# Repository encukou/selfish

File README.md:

# Selfish keyboard

This is an experiment.

Selfish layout for Moonlander is [here](https://configure.zsa.io/moonlander/layouts/DapMK/latest/0),
or, with some tweaks the configurator can't do, in [my QMK fork](https://github.com/encukou/qmk_firmware/blob/selfish/keyboards/moonlander/keymaps/selfish/keymap.c).

## Thanks

Thank you to Peter Lyons for sharing
[Squeezebox](https://peterlyons.com/problog/2022/01/squeezebox-keyboard-v2112/)!

## Legal stuff

Any file in this repository may be used either under the MIT licence or the
CC-BY-SA-40 licence, at your choice.
Please link to https://github.com/encukou/selfish for attribution.

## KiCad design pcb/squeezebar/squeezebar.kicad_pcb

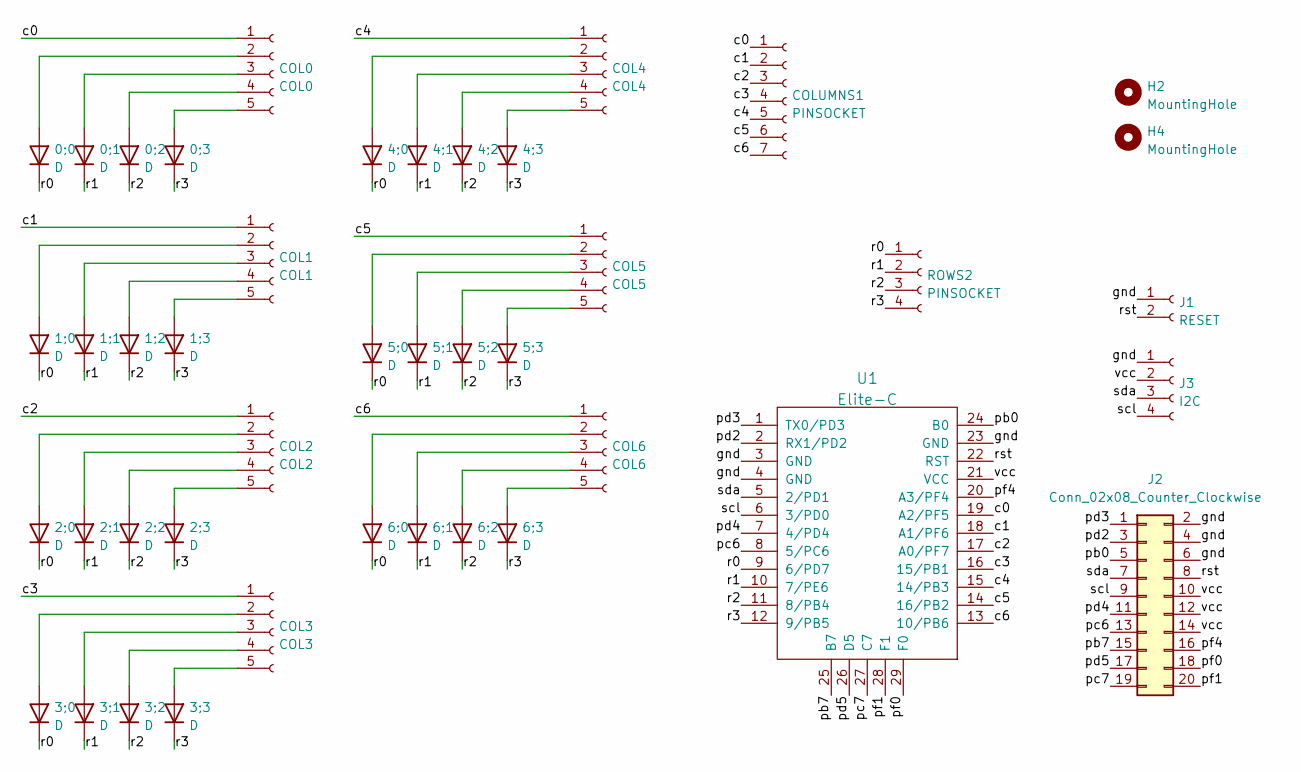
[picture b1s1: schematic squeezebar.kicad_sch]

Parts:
0;0, 0;1, 0;2, 0;3, 1;0, 1;1, 1;2, 1;3, 2;0, 2;1, 2;2, 2;3, 3;0, 3;1, 3;2, 3;3, 4;0, 4;1, 4;2, 4;3, 5;0, 5;1, 5;2, 5;3, 6;0, 6;1, 6;2, 6;3: D; Diode
COL0: COL0; PinHeader_Col_1x05_P2.54mm_Vertical
COL1: COL1; PinHeader_Col_1x05_P2.54mm_Vertical
COL2: COL2; PinHeader_Col_1x05_P2.54mm_Vertical
COL3: COL3; PinHeader_Col_1x05_P2.54mm_Vertical
COL4: COL4; PinHeader_Col_1x05_P2.54mm_Vertical
COL5: COL5; PinHeader_Col_1x05_P2.54mm_Vertical
COL6: COL6; PinHeader_Col_1x05_P2.54mm_Vertical
COLUMNS1: PINSOCKET; PinHeader_COLS_1x07_P2.54mm_Vertical
H2, H4: MountingHole; MountingHole_3.2mm_M3_DIN965
J1: RESET; PinHeader_RST_1x02_P2.54mm_Vertical
J2: Conn_02x08_Counter_Clockwise; PinSocket_2x10_P2.54mm_Vertical
J3: I2C; PinHeader_I2C_1x04_P2.54mm_Vertical
ROWS2: PINSOCKET; PinSocket_1x04_P2.54mm_Vertical_LongPads
U1: Elite-C

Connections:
/c0: COL0.1, COLUMNS1.1, U1.19 (A2/PF5)
/c1: COL1.1, COLUMNS1.2, U1.18 (A1/PF6)
/c2: COL2.1, COLUMNS1.3, U1.17 (A0/PF7)
/c3: COL3.1, COLUMNS1.4, U1.16 (15/PB1)
/c4: COL4.1, COLUMNS1.5, U1.15 (14/PB3)
/c5: COL5.1, COLUMNS1.6, U1.14 (16/PB2)
/c6: COL6.1, COLUMNS1.7, U1.13 (10/PB6)
/gnd: J1.1, J2.2, J2.4, J2.6, J3.1, U1.3 (GND), U1.4 (GND), U1.23 (GND)
/pb0: J2.5, U1.24 (B0)
/pb7: J2.15, U1.25 (B7)
/pc6: J2.13, U1.8 (5/PC6)
/pc7: J2.19, U1.27 (C7)
/pd2: J2.3, U1.2 (RX1/PD2)
/pd3: J2.1, U1.1 (TX0/PD3)
/pd4: J2.11, U1.7 (4/PD4)
/pd5: J2.17, U1.26 (D5)
/pf0: J2.18, U1.29 (F0)
/pf1: J2.20, U1.28 (F1)
/pf4: J2.16, U1.20 (A3/PF4)
/r0: 0;0.1 (K), 1;0.1 (K), 2;0.1 (K), 3;0.1 (K), 4;0.1 (K), 5;0.1 (K), 6;0.1 (K), ROWS2.1, U1.9 (6/PD7)
/r1: 0;1.1 (K), 1;1.1 (K), 2;1.1 (K), 3;1.1 (K), 4;1.1 (K), 5;1.1 (K), 6;1.1 (K), ROWS2.2, U1.10 (7/PE6)
/r2: 0;2.1 (K), 1;2.1 (K), 2;2.1 (K), 3;2.1 (K), 4;2.1 (K), 5;2.1 (K), 6;2.1 (K), ROWS2.3, U1.11 (8/PB4)
/r3: 0;3.1 (K), 1;3.1 (K), 2;3.1 (K), 3;3.1 (K), 4;3.1 (K), 5;3.1 (K), 6;3.1 (K), ROWS2.4, U1.12 (9/PB5)
/rst: J1.2, J2.8, U1.22 (RST)
/scl: J2.9, J3.4, U1.6 (3/PD0)
/sda: J2.7, J3.3, U1.5 (2/PD1)
/vcc: J2.10, J2.12, J2.14, J3.2, U1.21 (VCC)
unnamed: 0;0.2 (A), COL0.2
unnamed: 0;1.2 (A), COL0.3
unnamed: 0;2.2 (A), COL0.4
unnamed: 0;3.2 (A), COL0.5
unnamed: 1;0.2 (A), COL1.2
unnamed: 1;1.2 (A), COL1.3
unnamed: 1;2.2 (A), COL1.4
unnamed: 1;3.2 (A), COL1.5
unnamed: 2;0.2 (A), COL2.2
unnamed: 2;1.2 (A), COL2.3
unnamed: 2;2.2 (A), COL2.4
unnamed: 2;3.2 (A), COL2.5
unnamed: 3;0.2 (A), COL3.2
unnamed: 3;1.2 (A), COL3.3
unnamed: 3;2.2 (A), COL3.4
unnamed: 3;3.2 (A), COL3.5
unnamed: 4;0.2 (A), COL4.2
unnamed: 4;1.2 (A), COL4.3
unnamed: 4;2.2 (A), COL4.4
unnamed: 4;3.2 (A), COL4.5
unnamed: 5;0.2 (A), COL5.2
unnamed: 5;1.2 (A), COL5.3
unnamed: 5;2.2 (A), COL5.4
unnamed: 5;3.2 (A), COL5.5
unnamed: 6;0.2 (A), COL6.2
unnamed: 6;1.2 (A), COL6.3
unnamed: 6;2.2 (A), COL6.4
unnamed: 6;3.2 (A), COL6.5

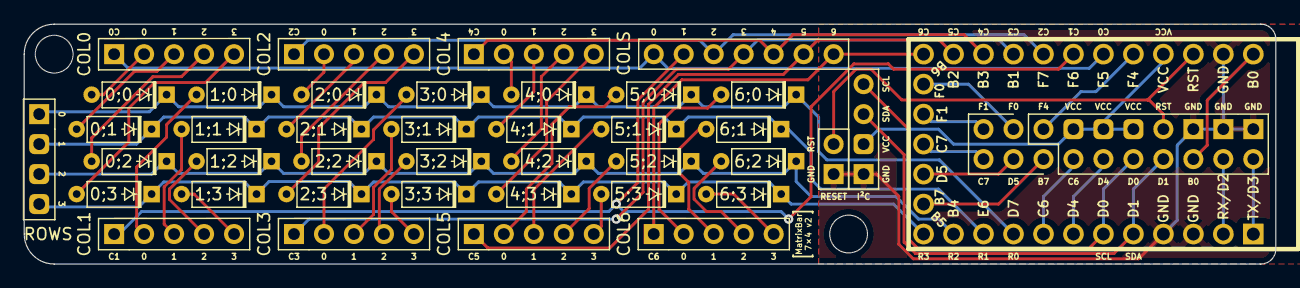
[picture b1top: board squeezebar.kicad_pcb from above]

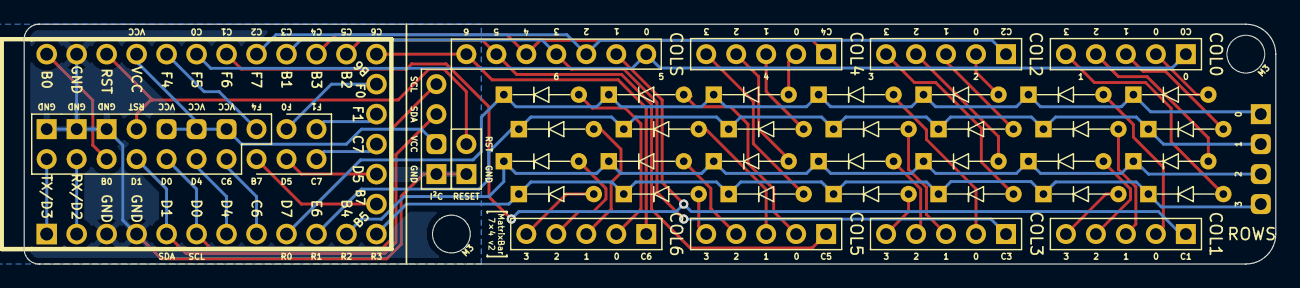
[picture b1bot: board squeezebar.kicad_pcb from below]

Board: 2 copper layers, 106.0 x 20.3 mm, 43 parts (2 on the bottom side), 55 nets.

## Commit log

2022-02-18 Add a Choc keyswitch well and an experimental keycap
2022-03-10 Refine cap & join 3 keywells
2022-03-10 Add wire clips
2022-03-10 Add diode grooves
2022-03-10 Improve parametrization & remove unnecessary parts from end wells
2022-03-10 Add mount pads
2022-03-10 Set smaller row spacing
2022-03-31 Add Squeezebox-style "saxophone" bottom row angle
2022-03-31 Rename finger column model
2022-03-31 Replace FreeCAD keycap model with an OpenSCAD one
2022-03-31 Add README & license
2022-03-31 Add links to Moonlander layout
2022-04-05 Adjust connectors so the middle keyswitch can fit
2022-04-06 Redesign the mounting pads
2022-06-03 Remove unused variables
2022-06-16 Add KiCAD PCB for a diode/connector bar for a Squeezebox-style keyboard
2022-06-16 Add mounting holes & extra side connectors
2022-06-17 squeezebar: Switch to a more regular layout (WIP)
2022-06-17 Squeezebar: New layout
2022-06-18 Squeezebar (Matrix Daughterboard): Compact layout
2022-06-18 Add numbers for mounting holes
2022-06-19 Squeezebar PCB: Add MCU. It's no longer a daughterboard...
2022-06-20 MatrixBar: Use Pro Micro pins for the rows/cols
2022-06-20 Round corners
2022-06-20 Switch to M3 screws
2022-06-20 Remove files that shouldn't really be in Git
2022-06-21 Rename to "MatrixBar"
2022-06-21 Add .gitignore for KiCad PCBs
2022-06-29 Reassign pins; break out I²C & RST at the expense of 2 mounting holes
2022-06-30 Move mounting hole from under the MCU
